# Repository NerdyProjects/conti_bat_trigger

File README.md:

## Contiakku Triggerplatine

Die Conti-Akkus aus dem Finger-Forum liegen immer noch rum, eine Platine muss her, damit es einfach wird.

[Foren Thread: Conti-Akku, Technikfaden](https://www.fingers-welt.de/phpBB/viewtopic.php?t=19876)

**Status: Untested**

### Funktionalität
* 4,8mm Flachstecker auf der Platine, die direkt auf den Akkustecker passen (zusätzliches Gehäuse empfehlenswert, da ohne kein Verpolschutz!)
* ESP32-C3 Supermini als Basis: Billig, einfach, mit CAN, USB, Wlan.
* Versorgung vom Akkupack oder Charger
* Trigger des Wakeups auf 12V oder 0V
* Trigger des Wakeups auf 12V für Akkus im Deepsleep, wenn Ladegerät angeschlossen
* Wachhalten per CAN

### Timeline
* Mitte Mai: PCB Bestellung
* Bis Ende Mai: Erste Tests geplant

## Errata
### HW v1 (Prod. 2026-05-06)
 * Fehlender Widerstand am Wakeup-Pullup. Wenn Pullup und Pulldown gleichzeitig aktiviert werden würden, kommt es zum Kurzschluss. Abhilfe: Leiterbahn zwischen D13 und R13 durchtrennen, einen Widerstand 1-5k darüber löten. Der passt gut auf die Pads mit drauf. Alternativ den Trace zwischen R15 und D13 (der von Q3 zu D3 geht) durchtrennen, etwas Lötstopp wegkratzen und dort die 1-3k einlöten.
 * Spannungsregler ist immer an - der Conti-Akku gibt auch im Aus-Zustand etwas Spannung am Batterie-Pin aus. Das reicht um die Platine "halb" zu starten - der ESP hat keinen Strom, aber die LED leuchtet. Führt zu höherem Ruhestrom bei gesteckter Platine.

 ### HW v2 (Prod. 2025-05-29)
 * Spannungsregler Enable ist auf etwa 7,5V Einschaltschwelle konfiguriert, allerdings gibt der Akku eine Leerlaufspannung von knapp 16V aus im abgeschalteten Zustand. Leider startet der Spannungsregler dann immernoch, die Platine braucht wenige mA Strom. Damit die Platine sowohl Lade-Wakeup (Versorgung per BAT+) und Entladewakeup (Versorgung über 12Vout) kann, gibt es hier leider keine sinnvolle Einschaltschwelle, ich habe keine Lösung für das Problem.

 ### Aufbau
 #### Charge Only
 * Nur als Ladewachhalter, lädt ?max. 8 Stunden oder bis Akku voll; jedenfalls länger als 1 Stunde?.
 * Achtung: Der Akku stoppt den Ladevorgang scheinbar nicht selbstständig! Überladegefahr!

 Von links nach rechts:
 * R3: 0 Ohm - 1 kOhm
 * R11: 470 kOhm zum Entladen vom Wakeup-Kurzschluss-Trigger-Kondensator
 * Q4 diagonal: 1-10µF Wakeup-Kurzschluss-Trigger-Kondensator
 * D3: 12V Zenerdiode, Strich nach links (Durchlassrichtung rechts nach links)
 * Q1: Brücke von Pin 2 nach 3

 #### ESP Bestückung

 Ganz wichtig: Reihenfolge beachten, sonst kommt man nicht mehr an die Pads dran.

 1. Stiftleisten auf Platine löten - ggf. zum richtigen Abstand halten den ESP bzw. die Adapterplatine schon oben auflegen
 2. Flachstecker bestücken (siehe unten)
 3. Sofern der Display-Adapter zum Einsatz kommt, nun die oberen Stiftleisten hier anlöten - ovale Pads. Achtung: Die obere Reihe kollidiert sehr schnell mit den Flachsteckern, kurze Seite der Stiftleiste nach unten bzw. nachkürzen!
 4. Display Adapter auf Platine löten, dabei nochmal genau mit allen Abständen schauen, ggf. etwas hoch stehen lassen, wenn Flachstecker zu weit hochschauen.
 5. ESP auf Displayadapter bzw. Platine löten - genau darauf achten, dass unterhalb kein Kurzschluss entsteht - ggf. etwas mehr Abstand lassen.

So sieht das aus, wenn man in der falschen Reihenfolge lötet. Mit etwas mehr Abstand noch rettbar :-)

Und fertig, mit Oled und der ersten Software:

 #### Flachstecker-Bestückung

 * Flachstecker am besten in einen Conti-Akku stecken. Soweit bekannt, passiert hier bei Kurzschlüssen nichts.

 * Beim Anlöten der Platine darauf achten, die Flachstecker nicht ganz durchzustecken, alternativ muss später oben Abstand gehalten werden. Sprich: Insgesamt darauf achten, dass die Flachstecker am Ende keinen Kurzschluss mit der Platine darüber machen.

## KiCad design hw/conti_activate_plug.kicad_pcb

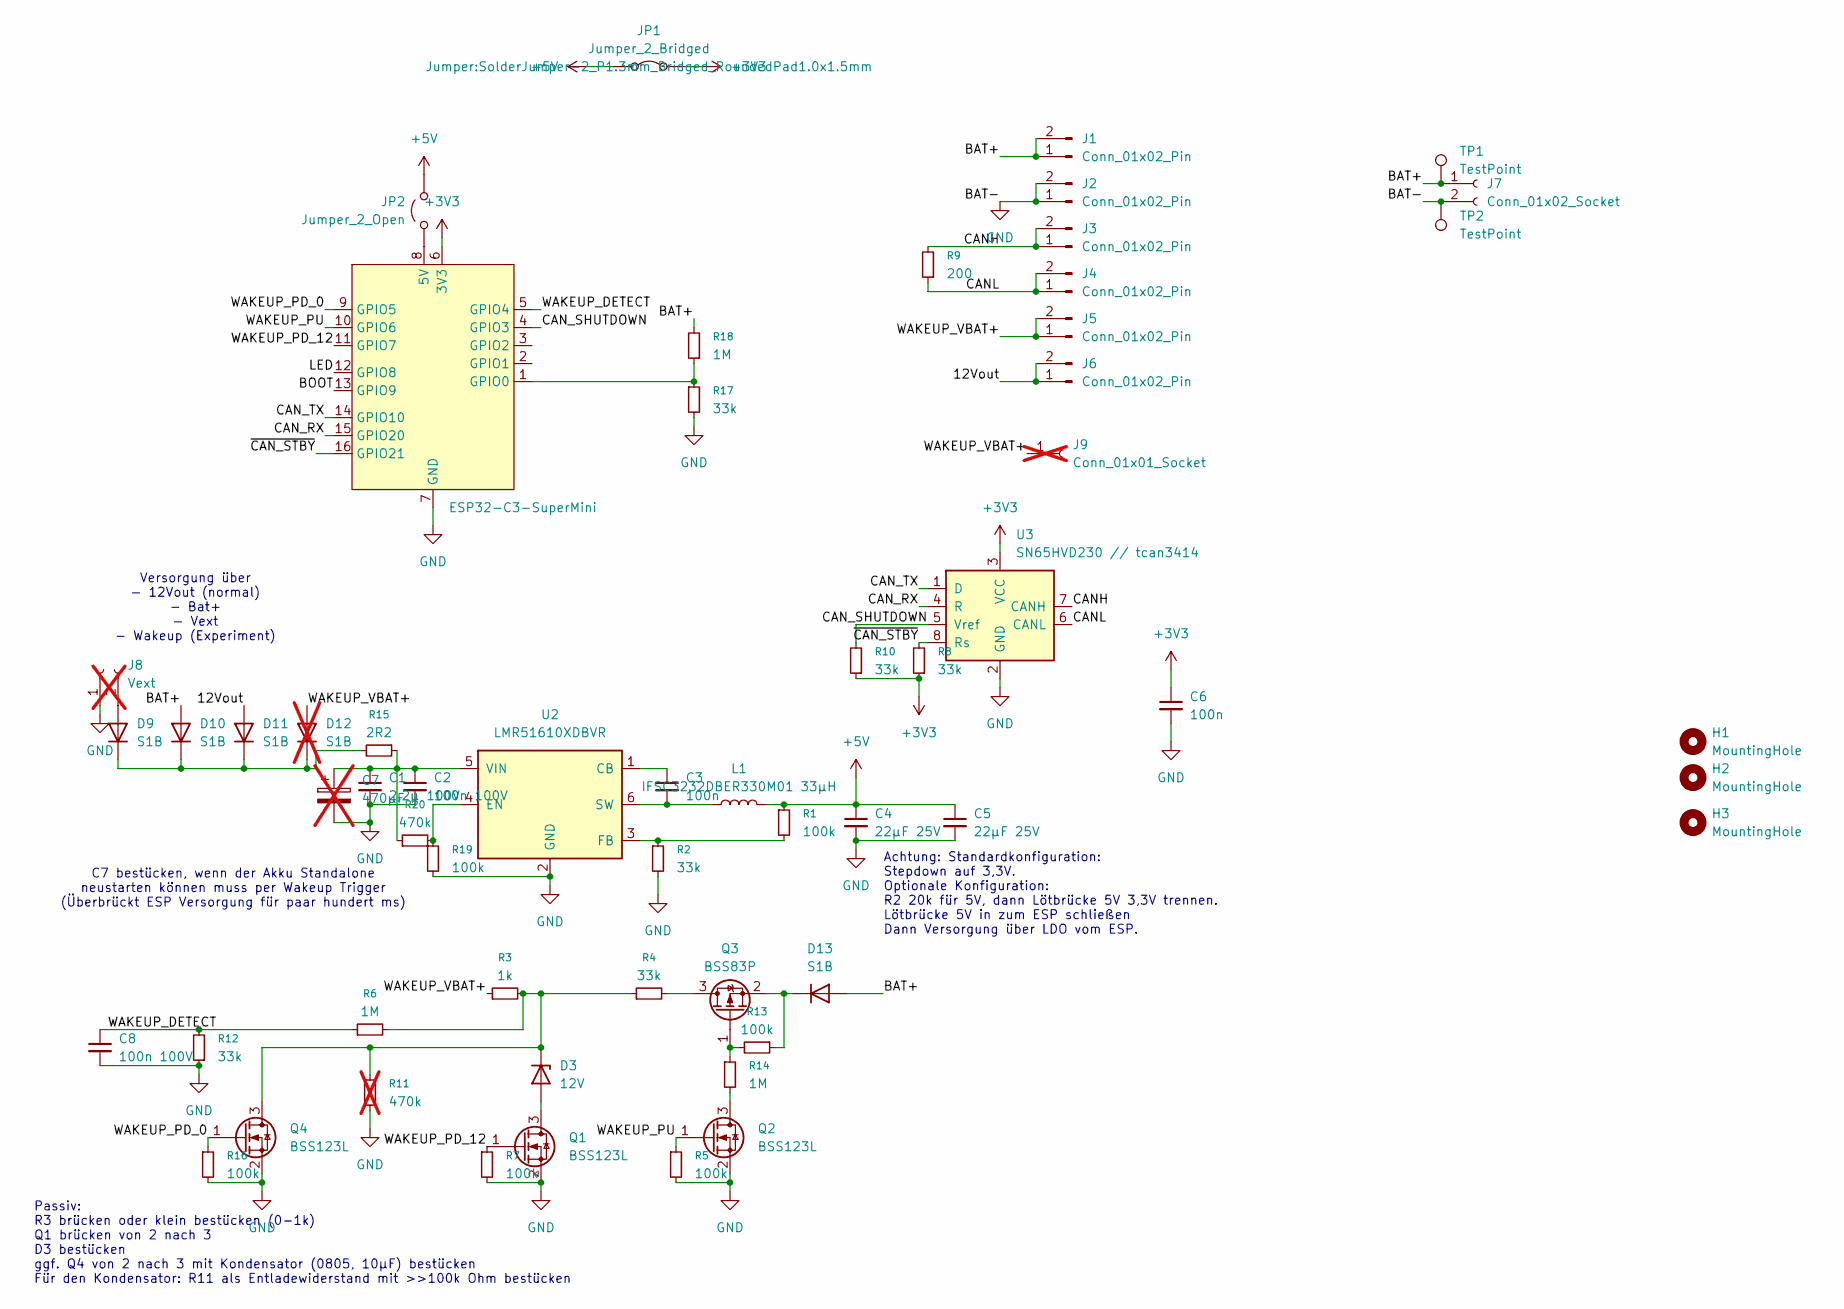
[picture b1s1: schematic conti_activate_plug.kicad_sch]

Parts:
C1: 2,2µ 100V; C_1206_3216Metric; LCSC C13585
C2, C8: 100n 100V; C_0603_1608Metric; LCSC C14663
C3, C6: 100n; C_0603_1608Metric; LCSC C14663
C4, C5: 22µF 25V; C_0805_2012Metric; LCSC C45783
C7: 470µF; CP_Radial_Tantal_D8.0mm_P5.00mm; not fitted
D3: 12V; D_SOD-123F; LCSC C22395569
D9, D10, D11, D13: S1B; D_SOD-123F; LCSC C64898
D12: S1B; D_SOD-123F; LCSC C64898; not fitted
H1, H2, H3: MountingHole; MountingHole_3.2mm_M3
J1, J2, J3, J4, J5, J6: Conn_01x02_Pin; 1x02_P5.08mm
J7: Conn_01x02_Socket; TerminalBlock_CUI_TB007-508-02_1x02_P5.08mm_Horizontal
J8: Vext; PinHeader_1x02_P2.54mm_Vertical; not fitted
J9: Conn_01x01_Socket; PinHeader_1x01_P2.54mm_Vertical; not fitted
JP1: Jumper_2_Bridged; SolderJumper-2_P1.3mm_Bridged_RoundedPad1.0x1.5mm
JP2: Jumper_2_Open; SolderJumper-2_P1.3mm_Open_RoundedPad1.0x1.5mm
L1: IFSC3232DBER330M01 33µH; L_Chilisin_BWVS00808040; LCSC C354641
Q1, Q2, Q4: BSS123L; SOT-23; LCSC C7420338
Q3: BSS83P; SOT-23; LCSC C7420340
R1, R5, R7, R13, R16, R19: 100k; R_0603_1608Metric; LCSC C25803
R2, R4, R8, R10, R12, R17: 33k; R_0603_1608Metric; LCSC C4216
R3: 1k; R_0603_1608Metric; LCSC C21190
R6, R14, R18: 1M; R_0603_1608Metric; LCSC C22935
R9: 200; R_0603_1608Metric; LCSC C8218
R11: 470k; R_0603_1608Metric; LCSC C23178; not fitted
R15: 2R2; R_0603_1608Metric; LCSC C22939
R20: 470k; R_0603_1608Metric; LCSC C23178
TP1, TP2: TestPoint; TestPoint_Loop_D3.80mm_Drill2.8mm
U1: ESP32-C3-SuperMini
U2: LMR51610XDBVR; SOT-23-6; LCSC C20539658
U3: SN65HVD230 // tcan3414; SOIC-8_3.9x4.9mm_P1.27mm; LCSC C12084

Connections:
+3V3: C6.1, JP1.2 (B), R8.1, R10.1, U1.6 (3V3), U3.3 (VCC)
+5V: C4.1, C5.1, JP1.1 (A), JP2.1 (A), L1.2, R1.1
/12Vout: D11.2 (A), J6.1, J6.2
/BAT+: D10.2 (A), D13.2 (A), J1.1, J1.2, J7.1, R18.2, TP1.1 (1_1)
/BOOT: U1.13 (GPIO9)
/CANH: J3.1, J3.2, R9.2, U3.7 (CANH)
/CANL: J4.1, J4.2, R9.1, U3.6 (CANL)
/CAN_RX: U1.15 (GPIO20), U3.4 (R)
/CAN_SHUTDOWN: R10.2, U1.4 (GPIO3), U3.5 (Vref)
/CAN_TX: U1.14 (GPIO10), U3.1 (D)
/LED: U1.12 (GPIO8)
/WAKEUP_DETECT: C8.1, R6.1, R12.2, U1.5 (GPIO4)
/WAKEUP_PD_0: Q4.1 (G), R16.1, U1.9 (GPIO5)
/WAKEUP_PD_12: Q1.1 (G), R7.1, U1.11 (GPIO7)
/WAKEUP_PU: Q2.1 (G), R5.1, U1.10 (GPIO6)
/WAKEUP_VBAT+: D12.2 (A), J5.1, J5.2, J9.1 (Pin_1_1), R3.1
/~CAN_STBY: R8.2, U1.16 (GPIO21), U3.8 (Rs)
GND: C1.2, C2.2, C4.2, C5.2, C6.2, C7.2, C8.2, J2.1, J2.2, J7.2, J8.1, Q1.2 (S), Q2.2 (S), Q4.2 (S), R2.2, R5.2, R7.2, R11.1, R12.1, R16.2, R17.2, R19.2, TP2.1 (1_1), U1.7 (GND), U2.2 (GND), U3.2 (GND)
unnamed: D3.2 (A), Q1.3 (D)
unnamed: D3.1 (K), Q4.3 (D), R3.2, R4.1, R6.2, R11.2
unnamed: D9.2 (A), J8.2
unnamed: D9.1 (K), D10.1 (K), D11.1 (K), D12.1 (K), R15.2
unnamed: D13.1 (K), Q3.2 (S), R13.1
unnamed: JP2.2 (B), U1.8 (5V)
unnamed: Q2.3 (D), R14.2
unnamed: Q3.3 (D), R4.2
unnamed: Q3.1 (G), R13.2, R14.1
unnamed: R17.1, R18.1, U1.1 (GPIO0)
unnamed: C3.1, U2.1 (CB)
unnamed: R19.1, R20.2, U2.4 (EN)
unnamed: R1.2, R2.1, U2.3 (FB)
unnamed: C3.2, L1.1, U2.6 (SW)
unnamed: C1.1, C2.1, C7.1, R15.1, R20.1, U2.5 (VIN)

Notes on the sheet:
C7 bestücken, wenn der Akku Standalone neustarten können muss per Wakeup Trigger (Überbrückt ESP Versorgung für paar hundert ms)
Passiv: R3 brücken oder klein bestücken (0-1k) Q1 brücken von 2 nach 3 D3 bestücken ggf. Q4 von 2 nach 3 mit Kondensator (0805, 10µF) bestücken Für den Kondensator: R11 als Entladewiderstand mit >>100k Ohm bestücken
Achtung: Standardkonfiguration: Stepdown auf 3,3V. Optionale Konfiguration: R2 20k für 5V, dann Lötbrücke 5V 3,3V trennen. Lötbrücke 5V in zum ESP schließen Dann Versorgung über LDO vom ESP.
Versorgung über - 12Vout (normal) - Bat+ - Vext - Wakeup (Experiment)

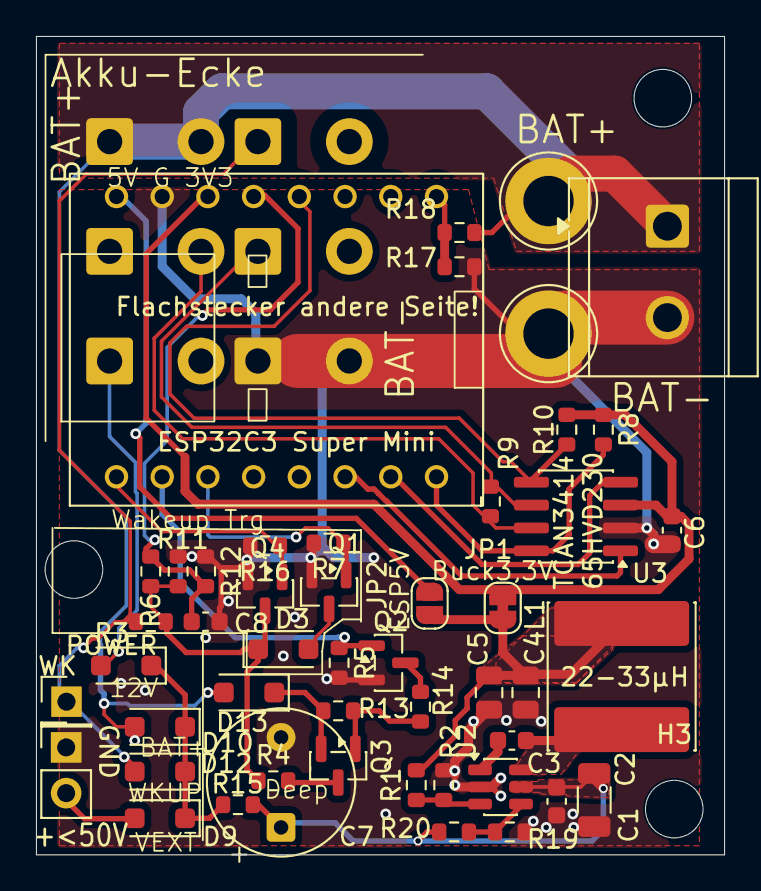
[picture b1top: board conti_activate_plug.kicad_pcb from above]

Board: 2 copper layers, 38.2 x 45.5 mm, 58 parts (0 on the bottom side), 31 nets.

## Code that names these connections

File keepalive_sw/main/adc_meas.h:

#pragma once
#include "sdkconfig.h"

/**
 * ADC pin definitions.
 *
 * VBAT_MEAS     (GPIO0): direct battery voltage, Vbat = Vmeas * 1033 / 33
 * WAKEUP_DETECT (GPIO4): voltage divider,        Vact = Vmeas * 1033 / 33
 * CAN_SHUTDOWN  (GPIO3): diagnostic pin voltage  (SuperMini only; on OLED
 *                        variant GPIO3 is a digital output)
 */
#define PIN_VBAT_MEAS      0  /**< GPIO0: battery voltage (both variants)   */
#define PIN_WAKEUP_DETECT  4  /**< GPIO4: wakeup detect (both variants)      */
#ifndef CONFIG_HW_VARIANT_OLED
#define PIN_CAN_SHUTDOWN   3  /**< GPIO3: CAN shutdown (SuperMini only)      */
#endif

/**
 * @brief Initialize ADC unit and calibration and start the sampling task.
 *        GPIO0 (Vbat) and GPIO4 (WakeupDetect) on both variants.
 *        GPIO3 (CAN_Shutdown) only on SuperMini.
 *
 * All conversions are performed by a single background task which caches the
 * results; the adc_get_*() accessors below only read that cache and never
 * touch the ADC hardware, so they are cheap and safe to call from any task.
 */
void adc_meas_init(void);

/**
 * @brief Latest cached battery voltage at GPIO0 (Vbat = Vmeas * 1033/33).
 * @return Actual battery voltage [V].
 */
float adc_get_vbat_voltage(void);

/**
 * @brief Latest cached Wakeup-Detect voltage (GPIO4, divider 1033/33).
 * @return Actual signal voltage [V].
 */
float adc_get_wakeup_detect_voltage(void);

int adc_get_vbat_percent(void);

#ifdef CONFIG_HW_VARIANT_OLED
/** CAN_SHUTDOWN ADC not available on OLED variant (GPIO3 is digital output). */
static inline float adc_get_can_shutdown_voltage(void) { return 0.0f; }
#else
/**
 * @brief Latest cached voltage at CAN_SHUTDOWN pin (GPIO3, SuperMini only).
 * @return Pin voltage [V].
 */
float adc_get_can_shutdown_voltage(void);
#endif

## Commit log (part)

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2026-04-21 Initial hw
2026-04-21 Readme
2026-04-21 Ordnerstruktur, PDF
2026-04-22 Vext, CAN Terminierung, Mounting-Hole
2026-04-23 Stepdown redesigned, TCAN3414, S1B
2026-04-24 paar Komponenten herausgesucht
2026-05-08 forgot hw/sch
2026-05-08 Errata v1
2026-06-10 Software for C3 SuperMini and Oled
2026-06-10 Bauanleitung
2026-06-16 display adapter
2026-06-16 schaltplan update
